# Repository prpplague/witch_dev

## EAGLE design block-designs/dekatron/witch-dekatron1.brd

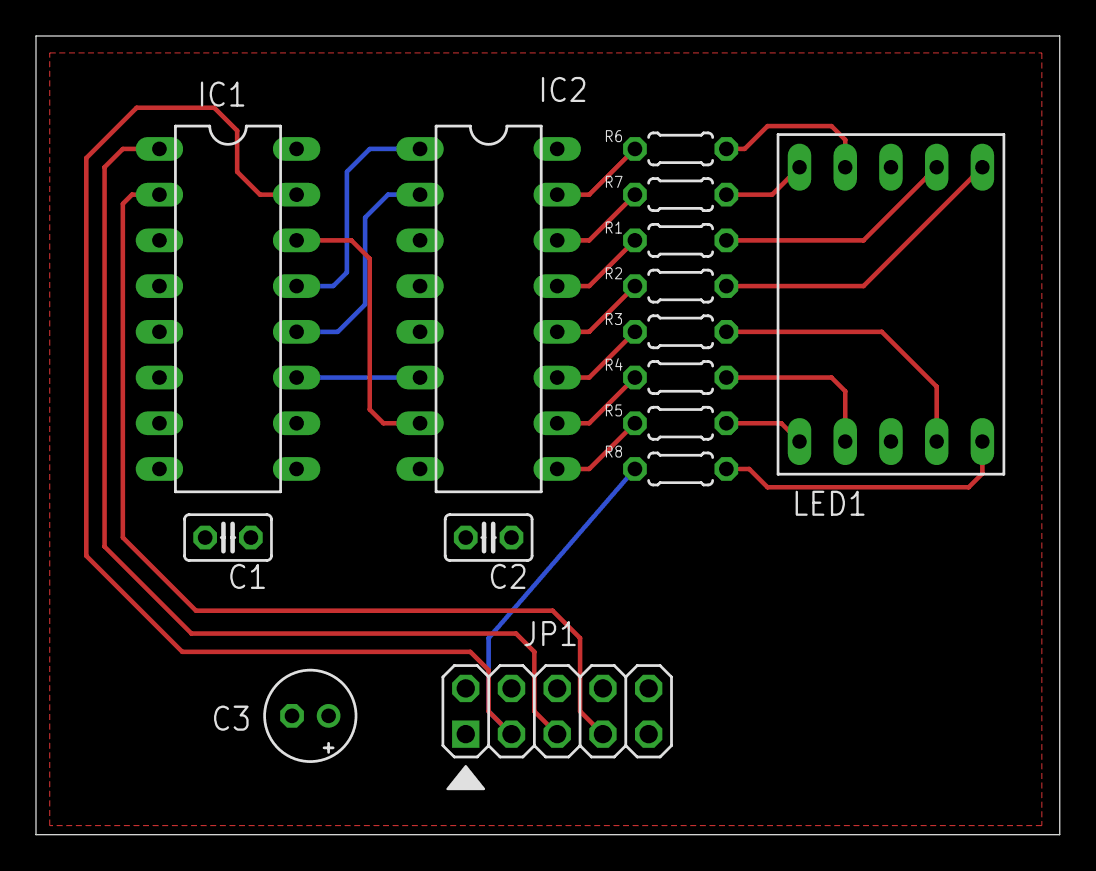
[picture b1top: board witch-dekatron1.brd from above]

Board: 2 copper layers, 56.9 x 44.4 mm, 15 parts (0 on the bottom side), 24 nets.

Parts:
C1, C2: C025-025X050
C3: E2-5
IC1: 74HC160N; DIL16
IC2: 4511N; DIL16
JP1: 2X05
LED1: 7-SEG_SA56-11; SA56-11
R1, R2, R3, R4, R5, R6, R7, R8: 330R; 0204/5

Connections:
unnamed: IC1.15, JP1.3, R8.2
unnamed: IC1.1, JP1.5
unnamed: IC2.13, R1.1
unnamed: IC2.12, R2.1
unnamed: IC2.11, R3.1
unnamed: IC2.10, R4.1
unnamed: IC2.9, R5.1
unnamed: IC2.15, R6.1
unnamed: IC2.14, R7.1
unnamed: IC1.14, IC2.7
unnamed: IC1.13, IC2.1
unnamed: IC1.12, IC2.2
unnamed: IC1.11, IC2.6
unnamed: LED1.7, R1.2
unnamed: LED1.6, R2.2
unnamed: LED1.4, R3.2
unnamed: LED1.2, R4.2
unnamed: LED1.1, R5.2
unnamed: LED1.9, R6.2
unnamed: LED1.10, R7.2
unnamed: LED1.5, R8.1
unnamed: IC1.2, JP1.7
VDD: C1.1, C2.1, C3.+, IC1.7, IC1.9, IC1.10, IC1.16, IC2.3, IC2.4, IC2.16, JP1.1
VSS: C1.2, C2.2, C3.-, IC1.8, IC2.5, IC2.8, JP1.9, LED1.3, LED1.8

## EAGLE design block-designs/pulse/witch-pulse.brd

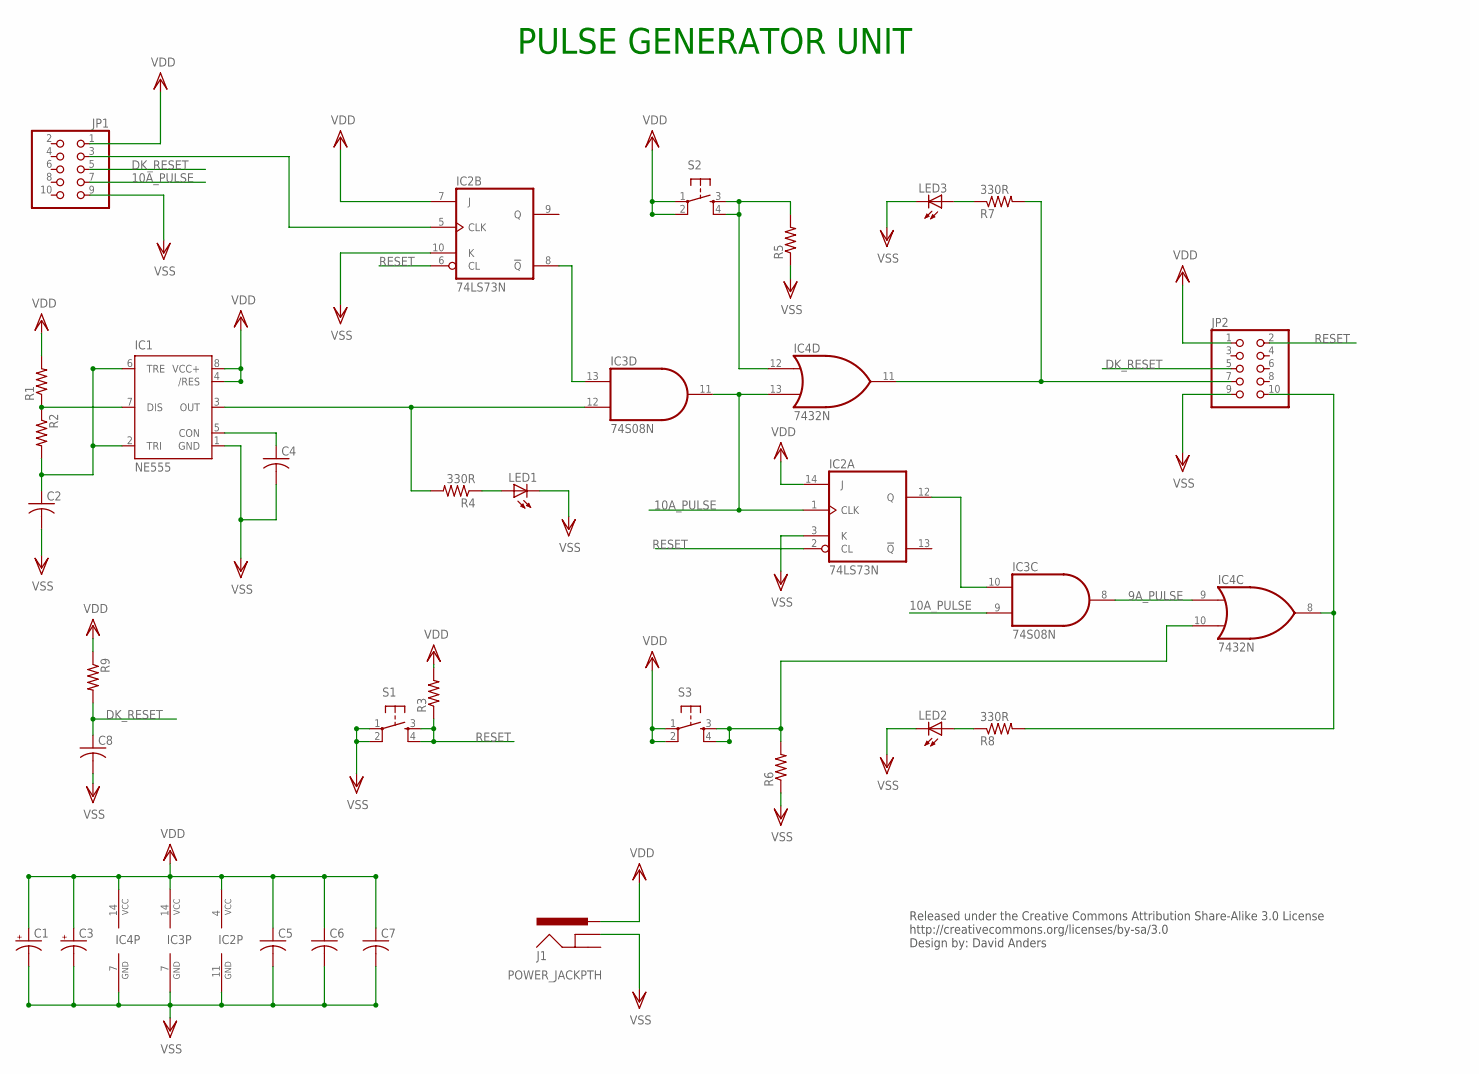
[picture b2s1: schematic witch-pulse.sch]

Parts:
C1, C3: CPOL-USE2.5-5; E2,5-5
C2, C8: C-US025-040X050; C025-040X050
C4, C5, C6, C7: C-US025-025X050; C025-025X050
IC1: NE555; DIL-08
IC2: 74LS73N; DIL14
IC3: 74S08N; DIL14
IC4: 7432N; DIL14
J1: POWER_JACKPTH; POWER_JACK_PTH
JP1, JP2: PINHD-2X5; 2X05
LED1, LED2, LED3: LED5MM
R1, R2, R3, R5, R6, R9: R-US_0204/5; 0204/5
R4, R7, R8: 330R; 0204/5
S1, S2, S3: TAC_SWITCHPTH; TACTILE-PTH

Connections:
9A_PULSE: IC3.8 (O), IC4.9 (I0)
10A_PULSE: IC2.1 (CLK), IC3.9 (I0), IC3.11 (O), IC4.13 (I1), JP1.7
DK_RESET: C8.1, JP1.5, JP2.5, R9.2
unnamed: IC1.3 (OUT), IC3.12 (I0), R4.2
unnamed: IC4.8 (O), JP2.10, R8.2
unnamed: IC2.8 (!Q), IC3.13 (I1)
unnamed: IC4.12 (I0), R5.2, S2.3, S2.4
unnamed: IC2.12 (Q), IC3.10 (I1)
unnamed: IC4.10 (I1), R6.2, S3.3, S3.4
unnamed: IC1.7 (DIS), R1.1, R2.1
unnamed: IC2.5 (CLK), JP1.3
unnamed: C2.1, IC1.2 (TRI), IC1.6 (TRE), R2.2
unnamed: C4.1, IC1.5 (CON)
unnamed: LED1.A, R4.1
unnamed: LED3.A, R7.1
unnamed: LED2.A, R8.1
unnamed: IC4.11 (O), JP2.7, R7.2
RESET: IC2.2 (CL), IC2.6 (CL), JP2.2, R3.1, S1.3, S1.4
VDD: C1.+, C3.+, C5.1, C6.1, C7.1, IC1.4 (/RES), IC1.8 (VCC+), IC2.4 (VCC), IC2.7 (J), IC2.14 (J), IC3.14 (VCC), IC4.14 (VCC), J1.PWR, JP1.1, JP2.1, R1.2, R3.2, R9.1, S2.1, S2.2, S3.1, S3.2
VSS: C1.-, C2.2, C3.-, C4.2, C5.2, C6.2, C7.2, C8.2, IC1.1 (GND), IC2.3 (K), IC2.10 (K), IC2.11 (GND), IC3.7 (GND), IC4.7 (GND), J1.GNDBREAK, JP1.9, JP2.9, LED1.K (C), LED2.K (C), LED3.K (C), R5.1, R6.1, S1.1, S1.2

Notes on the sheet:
Released under the Creative Commons Attribution Share-Alike 3.0 License http://creativecommons.org/licenses/by-sa/3.0 Design by: David Anders
PULSE GENERATOR UNIT

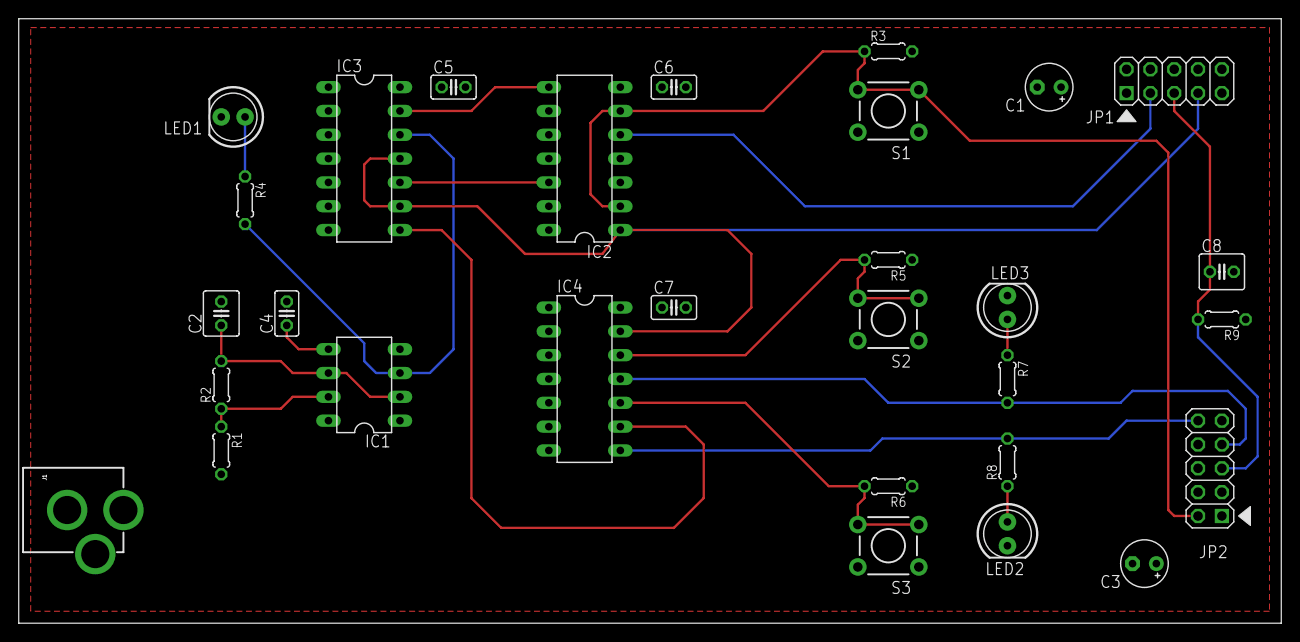
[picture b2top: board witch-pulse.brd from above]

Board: 2 copper layers, 134.6 x 64.4 mm, 30 parts (0 on the bottom side), 20 nets.

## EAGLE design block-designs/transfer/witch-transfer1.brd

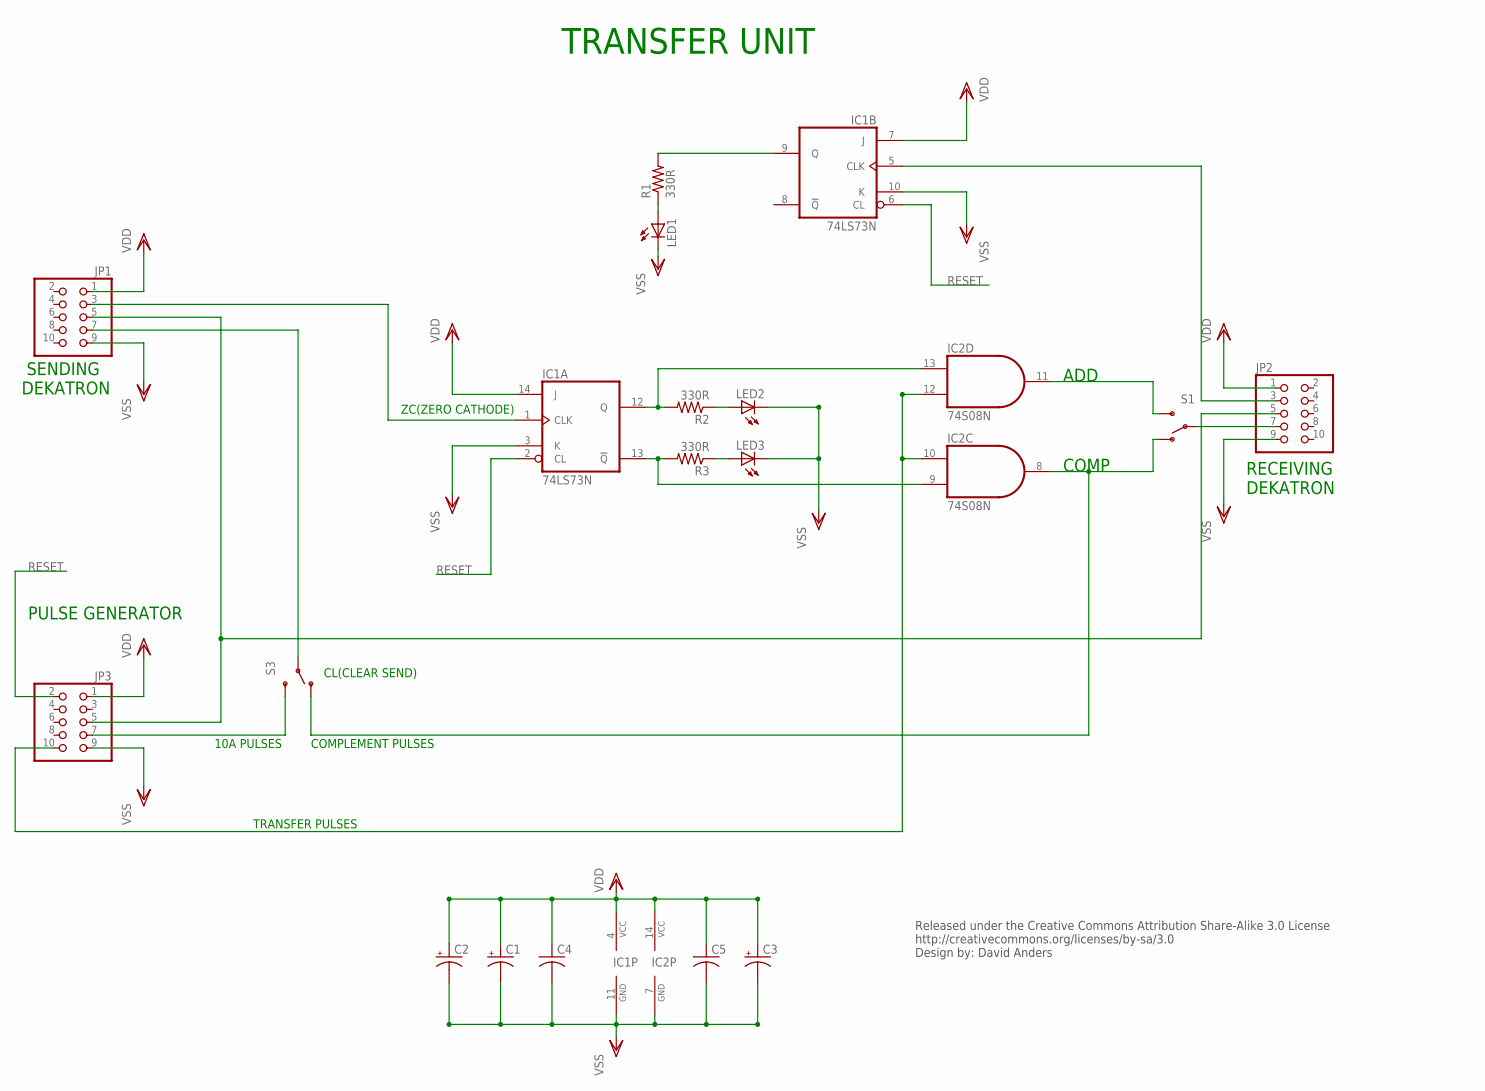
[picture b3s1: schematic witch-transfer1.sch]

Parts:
C1, C2, C3: CPOL-USE2-5; E2-5
C4, C5: C-US025-025X050; C025-025X050
IC1: 74LS73N; DIL14
IC2: 74S08N; DIL14
JP1, JP2, JP3: PINHD-2X5; 2X05
LED1, LED2, LED3: LED5MM
R1, R2, R3: 330R; 0204/5
S1, S3: SWITCH-SPDTPTH; SWITCH-SPDT

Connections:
unnamed: JP2.7, S1.2
unnamed: IC2.10 (I1), IC2.12 (I0), JP3.10
unnamed: IC1.13 (!Q), IC2.9 (I0), R3.2
unnamed: IC1.12 (Q), IC2.13 (I1), R2.2
unnamed: IC2.11 (O), S1.3 (S)
unnamed: LED2.A, R2.1
unnamed: LED3.A, R3.1
unnamed: LED1.A, R1.1
unnamed: JP3.7, S3.3 (S)
unnamed: IC1.5 (CLK), JP2.3
unnamed: IC1.9 (Q), R1.2
unnamed: JP1.5, JP2.5, JP3.5
unnamed: IC2.8 (O), S1.1 (O), S3.1 (O)
RESET: IC1.2 (CL), IC1.6 (CL), JP3.2
TRANSFER_PULSE: JP1.7, S3.2
VDD: C1.+, C2.+, C3.+, C4.1, C5.1, IC1.4 (VCC), IC1.7 (J), IC1.14 (J), IC2.14 (VCC), JP1.1, JP2.1, JP3.1
VSS: C1.-, C2.-, C3.-, C4.2, C5.2, IC1.3 (K), IC1.10 (K), IC1.11 (GND), IC2.7 (GND), JP1.9, JP2.9, JP3.9, LED1.K (C), LED2.K (C), LED3.K (C)
ZC_TX: IC1.1 (CLK), JP1.3

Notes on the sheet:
TRANSFER UNIT
ADD
COMP
Released under the Creative Commons Attribution Share-Alike 3.0 License http://creativecommons.org/licenses/by-sa/3.0 Design by: David Anders
SENDING DEKATRON
RECEIVING DEKATRON
ZC(ZERO CATHODE)
CL(CLEAR SEND)
10A PULSES
TRANSFER PULSES
COMPLEMENT PULSES
PULSE GENERATOR

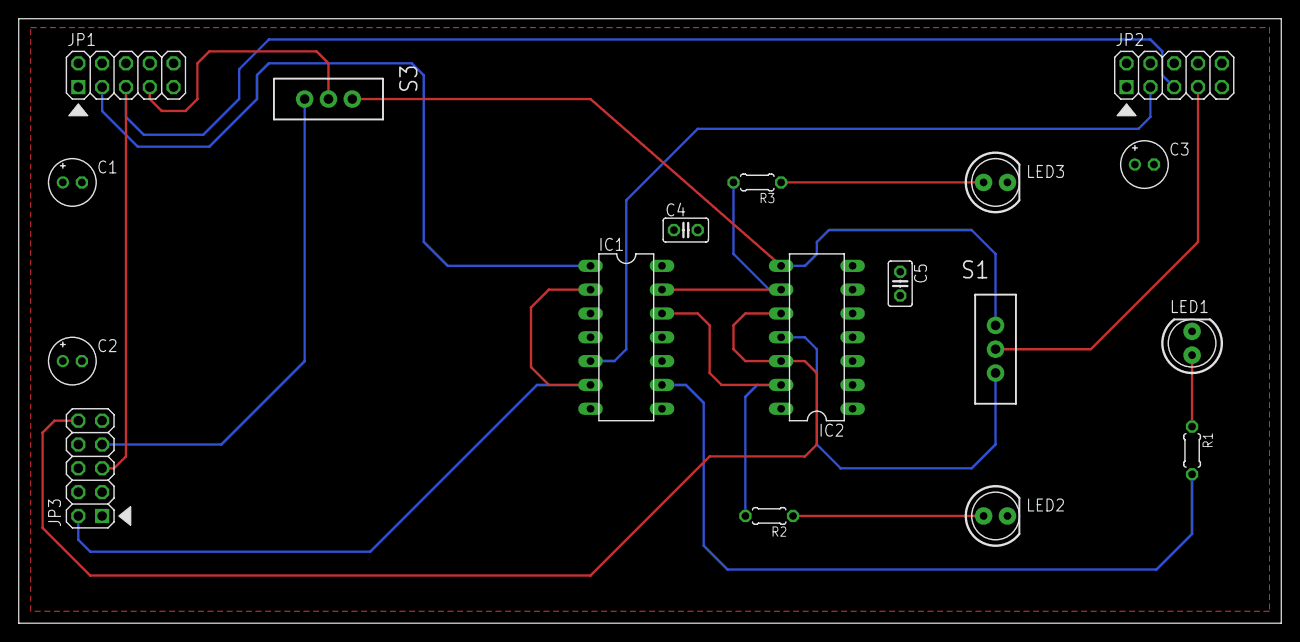
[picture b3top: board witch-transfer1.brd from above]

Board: 2 copper layers, 134.6 x 64.4 mm, 18 parts (0 on the bottom side), 18 nets.

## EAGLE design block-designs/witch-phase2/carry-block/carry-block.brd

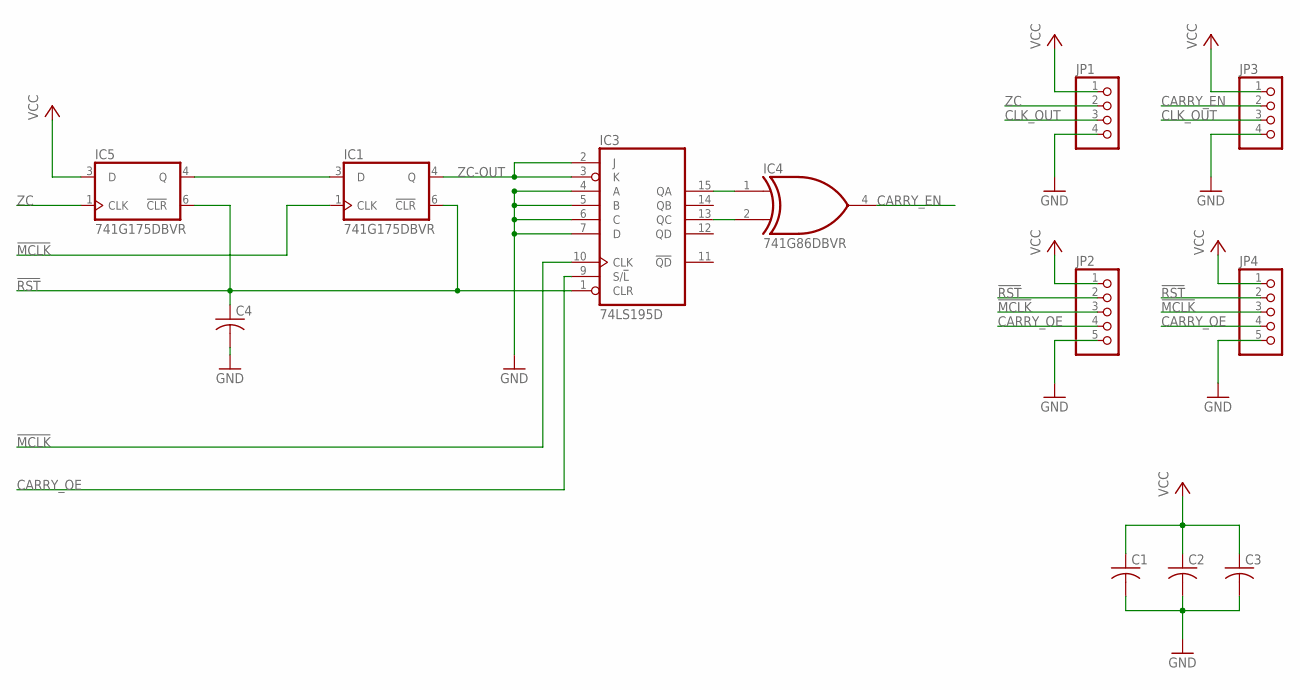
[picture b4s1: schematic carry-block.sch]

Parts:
C1, C2, C3, C4: C-USC0603K; C0603K
IC1, IC5: 741G175DBVR; DBV_R-PDSO-G6
IC3: 74LS195D; SO16
IC4: 741G86DBVR; SOT23-5
JP1, JP3: PINHD-1X4; 1X04
JP2, JP4: PINHD-1X5; 1X05

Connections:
!MCLK: IC1.1 (CLK), IC3.10 (CLK), JP2.3, JP4.3
!RST: C4.1, IC1.6 (!CLR), IC3.1 (CLR), IC5.6 (!CLR), JP2.2, JP4.2
CARRY_EN: IC4.4 (O), JP3.2
CARRY_OE: IC3.9 (S/!L), JP2.4, JP4.4
CLK_OUT: JP1.3, JP3.3
GND: C1.2, C2.2, C3.2, C4.2, IC1.2 (GND), IC3.4 (A), IC3.5 (B), IC3.6 (C), IC3.7 (D), IC3.8 (GND), IC4.3 (GND), IC5.2 (GND), JP1.4, JP2.5, JP3.4, JP4.5
unnamed: IC3.15 (QA), IC4.1 (I0)
unnamed: IC3.13 (QC), IC4.2 (I1)
unnamed: IC1.3 (D), IC5.4 (Q)
VCC: C1.1, C2.1, C3.1, IC1.5 (VCC), IC3.16 (VCC), IC4.5 (VCC), IC5.3 (D), IC5.5 (VCC), JP1.1, JP2.1, JP3.1, JP4.1
ZC: IC5.1 (CLK), JP1.2
ZC-OUT: IC1.4 (Q), IC3.2 (J), IC3.3 (K)

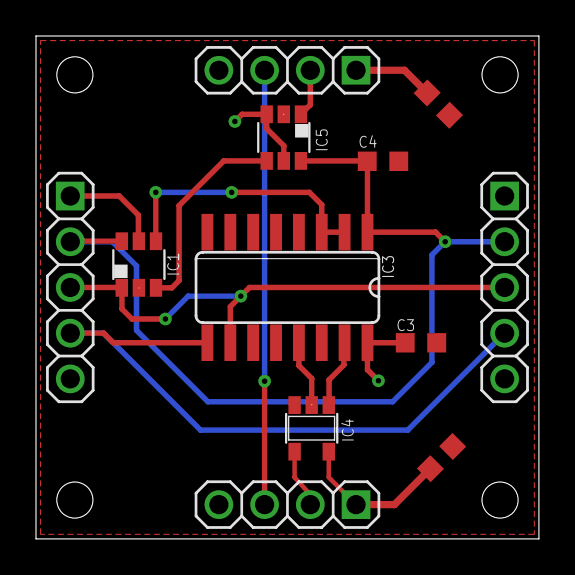
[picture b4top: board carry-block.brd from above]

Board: 2 copper layers, 27.9 x 27.9 mm, 12 parts (0 on the bottom side), 12 nets.

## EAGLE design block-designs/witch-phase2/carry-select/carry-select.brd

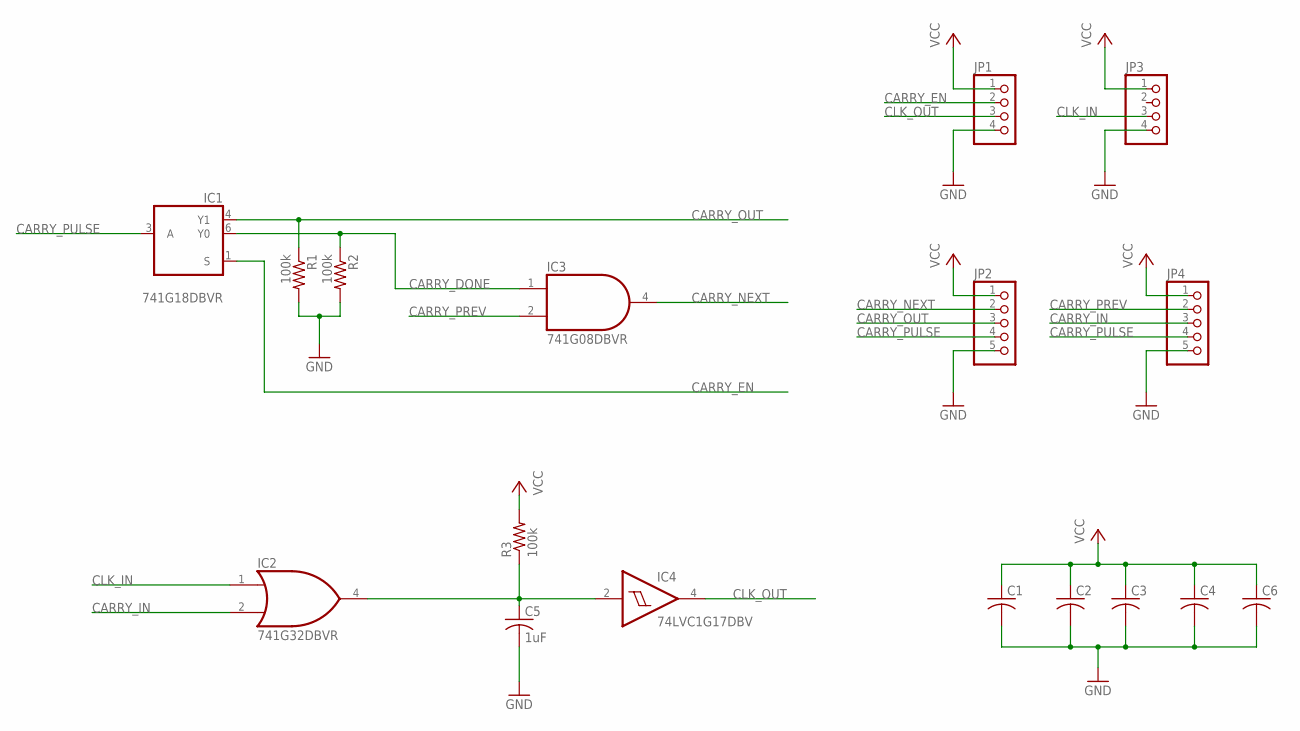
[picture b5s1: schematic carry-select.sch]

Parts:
C1, C2, C3, C4, C6: C-USC0603K; C0603K
C5: 1uF; C0603K
IC1: 741G18DBVR; DBV_R-PDSO-G6
IC2: 741G32DBVR; SOT23-5
IC3: 741G08DBVR; SOT23-5
IC4: 74LVC1G17DBV; SOT23-5
JP1, JP3: PINHD-1X4; 1X04
JP2, JP4: PINHD-1X5; 1X05
R1, R2, R3: 100k; R0603

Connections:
CARRY_DONE: IC1.6 (Y0), IC3.1 (I0), R2.1
CARRY_EN: IC1.1 (S), JP1.2
CARRY_IN: IC2.2 (I1), JP4.3
CARRY_NEXT: IC3.4 (O), JP2.2
CARRY_OUT: IC1.4 (Y1), JP2.3, R1.1
CARRY_PREV: IC3.2 (I1), JP4.2
CARRY_PULSE: IC1.3 (A), JP2.4, JP4.4
CLK_IN: IC2.1 (I0), JP3.3
CLK_OUT: IC4.4 (O), JP1.3
GND: C1.2, C2.2, C3.2, C4.2, C5.2, C6.2, IC1.2 (GND), IC2.3 (GND), IC3.3 (GND), IC4.3 (GND), JP1.4, JP2.5, JP3.4, JP4.5, R1.2, R2.2
PRE_CLK: C5.1, IC2.4 (O), IC4.2 (I), R3.1
VCC: C1.1, C2.1, C3.1, C4.1, C6.1, IC1.5 (VCC), IC2.5 (VCC), IC3.5 (VCC), IC4.5 (VCC), JP1.1, JP2.1, JP3.1, JP4.1, R3.2

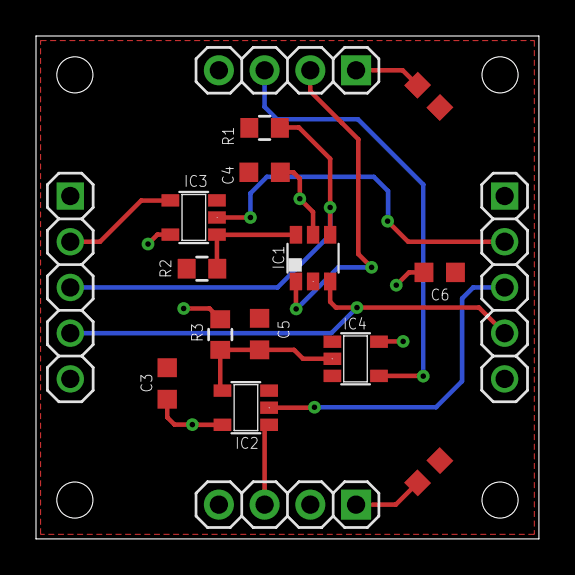
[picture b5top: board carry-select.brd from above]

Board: 2 copper layers, 27.9 x 27.9 mm, 17 parts (0 on the bottom side), 12 nets.

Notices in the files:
parts and their libraries:
SparkFun-Electromechanical: Licensing: CC v3.0 Share-Alike You are welcome to use this library for commercial purposes.
SparkFun-Connectors: Licensing: Creative Commons ShareAlike 4.0 International - https://creativecommons.org/licenses/by-sa/4.0
